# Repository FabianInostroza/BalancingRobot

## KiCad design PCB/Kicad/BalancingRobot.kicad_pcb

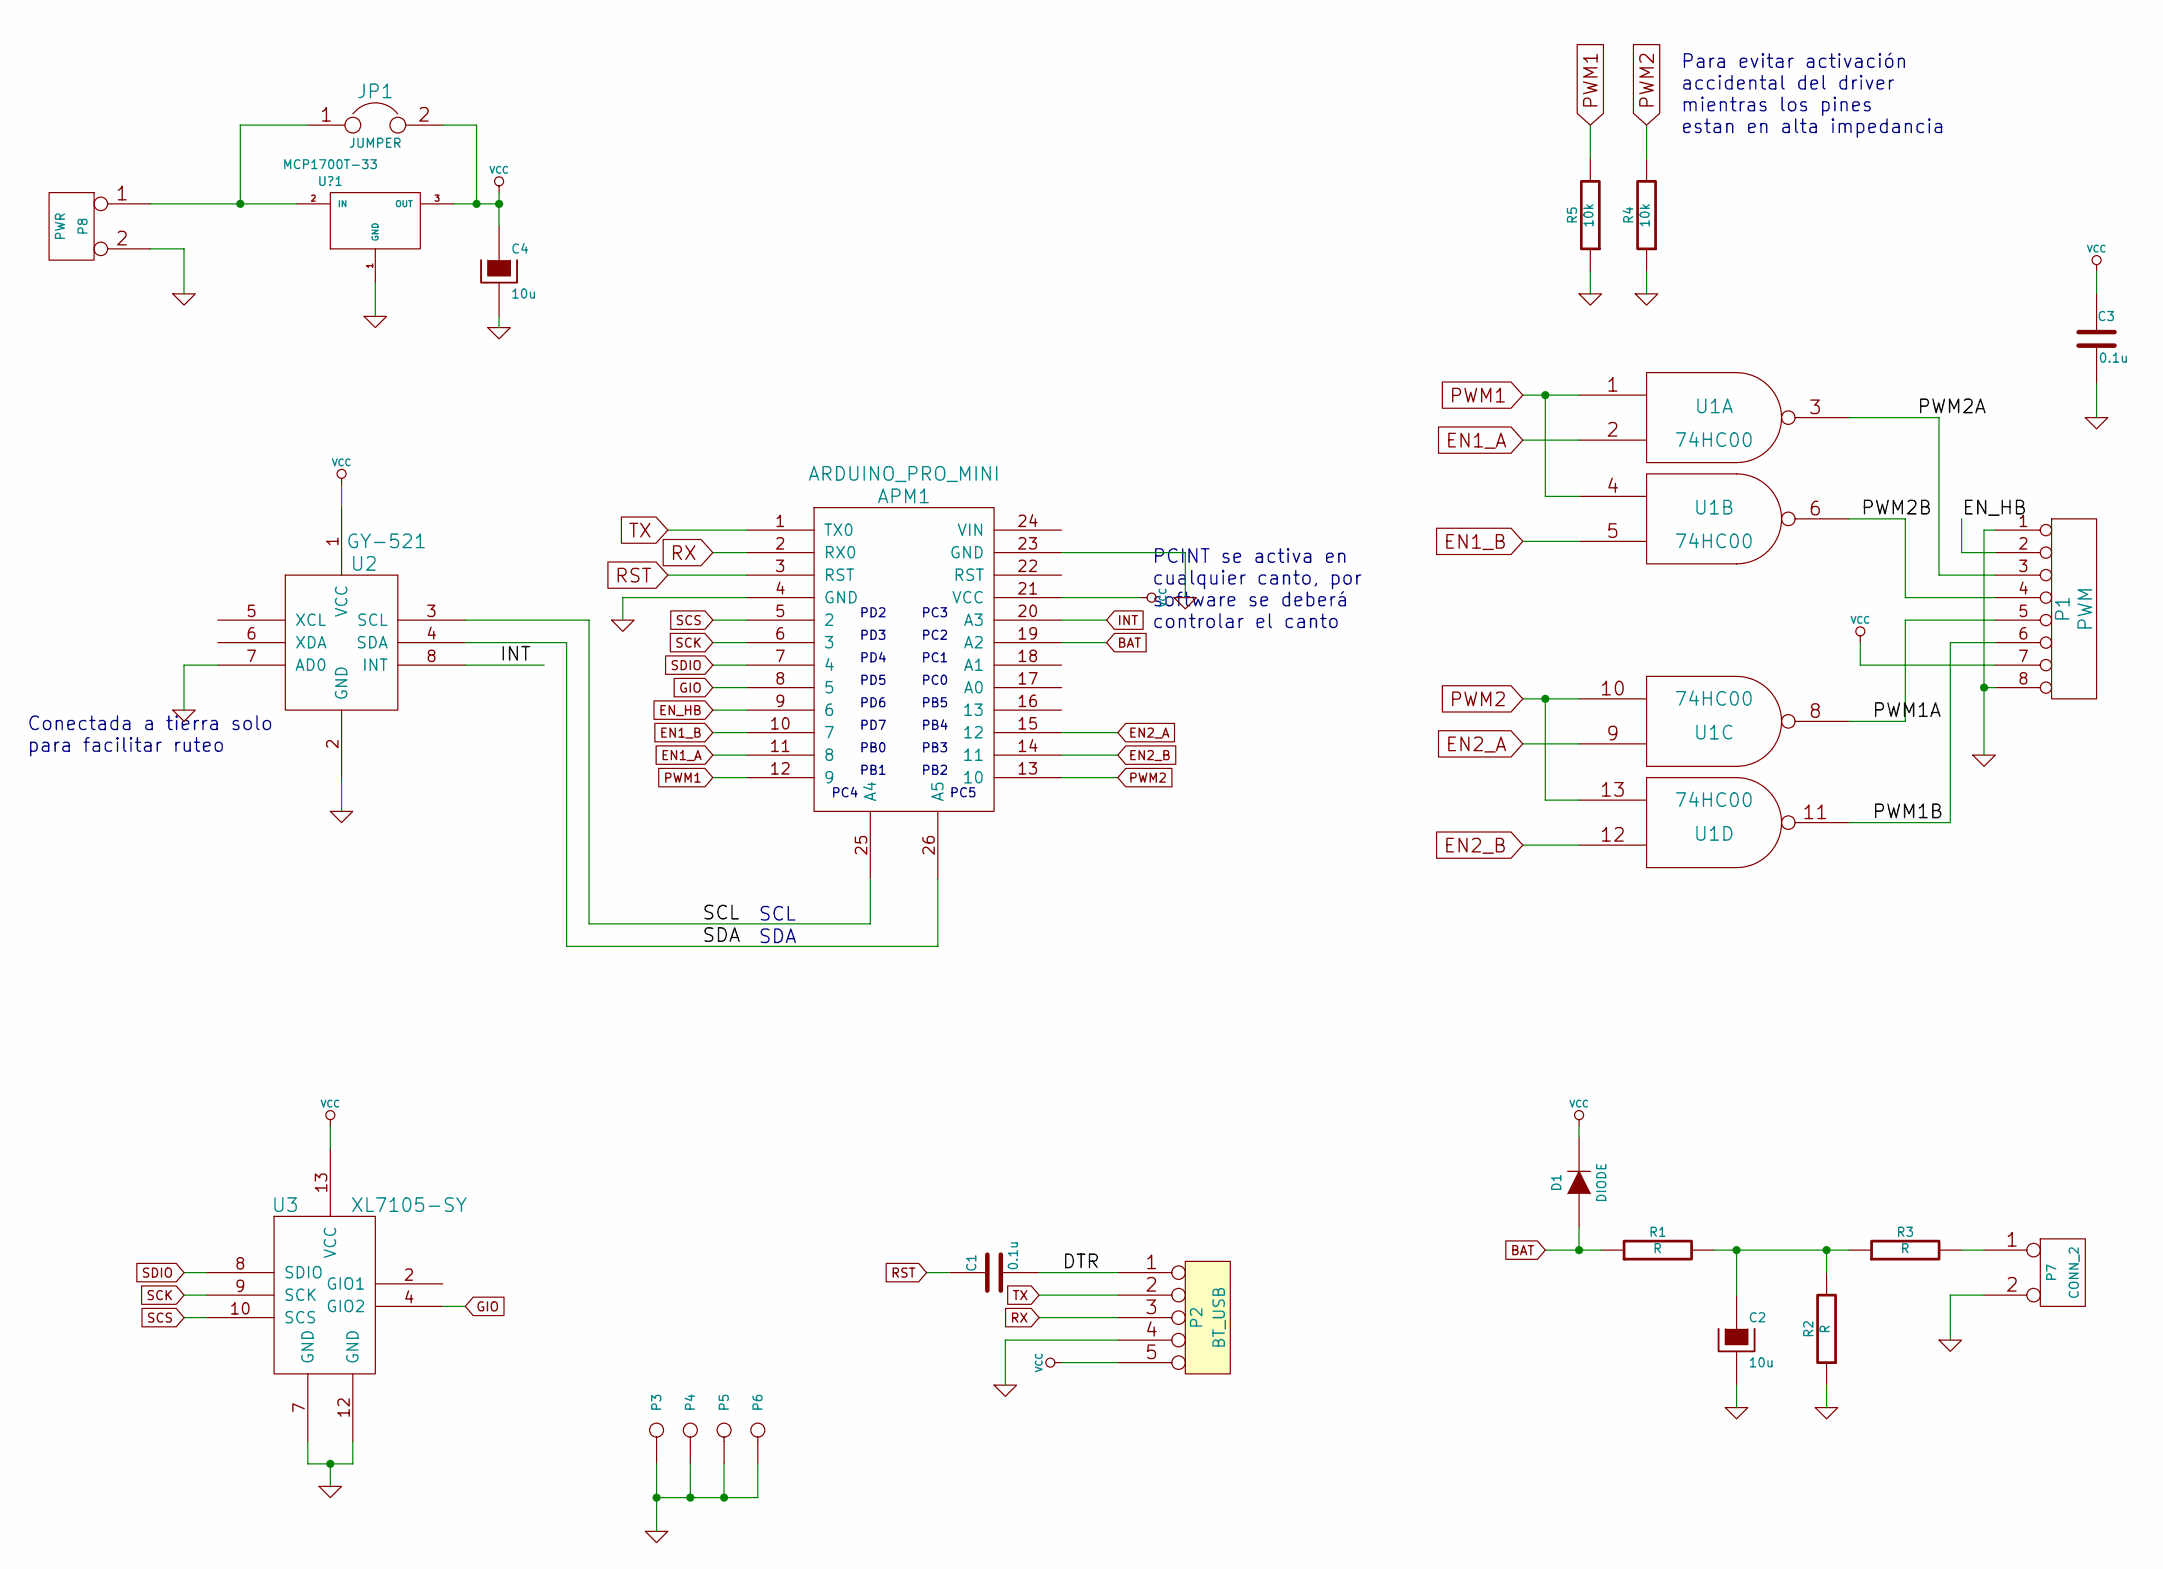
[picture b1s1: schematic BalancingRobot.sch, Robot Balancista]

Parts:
APM1: ARDUINO_PRO_MINI
C1, C3: 0.1u
C2, C4: 10u
D1: DIODE
JP1: JUMPER
P1: PWM
P2: BT_USB
P3, P4, P5, P6: CONN_1
P7: CONN_2
P8: PWR
R1, R2, R3: R
R4, R5: 10k
U1: 74HC00
U2: GY-521
U3: XL7105-SY
U?1: MCP1700T-33

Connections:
/DTR: C1.2, P2.1
/PWM1A: P1.5, U1.8
/PWM1B: P1.6, U1.11
/PWM2A: P1.3, U1.3
/PWM2B: P1.4, U1.6
/SCL: APM1.25 (A4), U2.3 (SCL)
/SDA: APM1.26 (A5), U2.4 (SDA)
BAT: APM1.19 (A2), D1.1 (A), R1.1
EN1_A: APM1.11 (8), U1.2
EN1_B: APM1.10 (7), U1.5
EN2_A: APM1.15 (12), U1.9
EN2_B: APM1.14 (11), U1.12
EN_HB: APM1.9 (6), P1.2
GIO: APM1.8 (5), U3.4 (GIO2)
GND: APM1.4 (GND), APM1.23 (GND), C2.2, C3.2, C4.2, P1.1, P1.8, P2.4, P3.1, P4.1, P5.1, P6.1, P7.2 (PM), P8.2 (PM), R2.1, R4.1, R5.1, U1.7 (GND), U2.2 (GND), U2.7 (AD0), U3.7 (GND), U3.12 (GND), U?1.1 (GND)
INT: APM1.20 (A3), U2.8 (INT)
unnamed: P7.1, R3.2
unnamed: C2.1, R1.2, R2.2, R3.1
unnamed: JP1.1, P8.1, U?1.2 (IN)
PWM1: APM1.12 (9), R5.2, U1.1, U1.4
PWM2: APM1.13 (10), R4.2, U1.10, U1.13
RST: APM1.3 (RST), C1.1
RX: APM1.2 (RX0), P2.3
SCK: APM1.6 (3), U3.9 (SCK)
SCS: APM1.5 (2), U3.10 (SCS)
SDIO: APM1.7 (4), U3.8 (SDIO)
TX: APM1.1 (TX0), P2.2
VCC: APM1.21 (VCC), C3.1, C4.1, D1.2 (K), JP1.2, P1.7, P2.5, U1.14 (VCC), U2.1 (VCC), U3.13 (VCC), U?1.3 (OUT)

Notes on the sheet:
SDA
SCL
Conectada a tierra solo para facilitar ruteo
PCINT se activa en cualquier canto, por software se deberá controlar el canto
PD2
PD3
PD4
PD5
PD6
PD7
PB0
PB1
PC3
PC2
PC1
PC0
PB5
PB4
PB3
PB2
PC4
PC5
Para evitar activación accidental del driver mientras los pines estan en alta impedancia

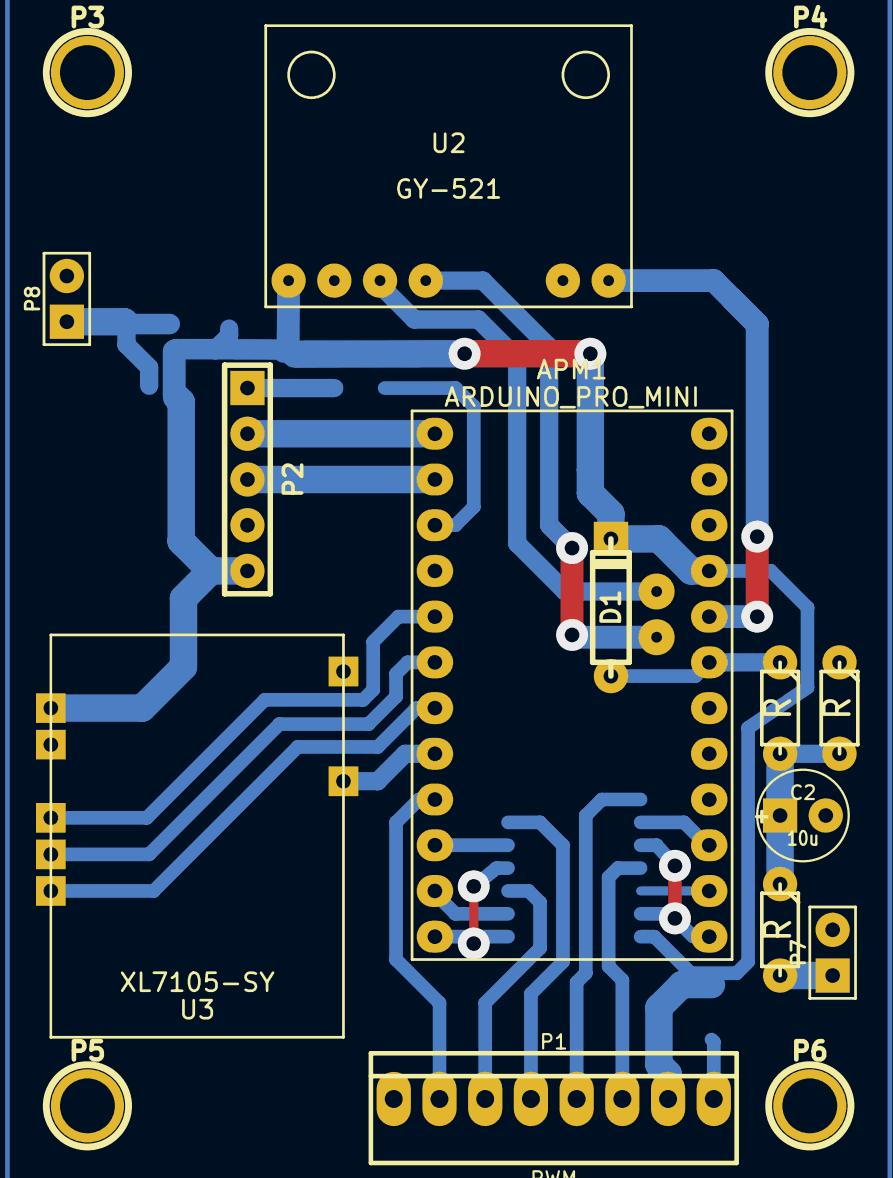
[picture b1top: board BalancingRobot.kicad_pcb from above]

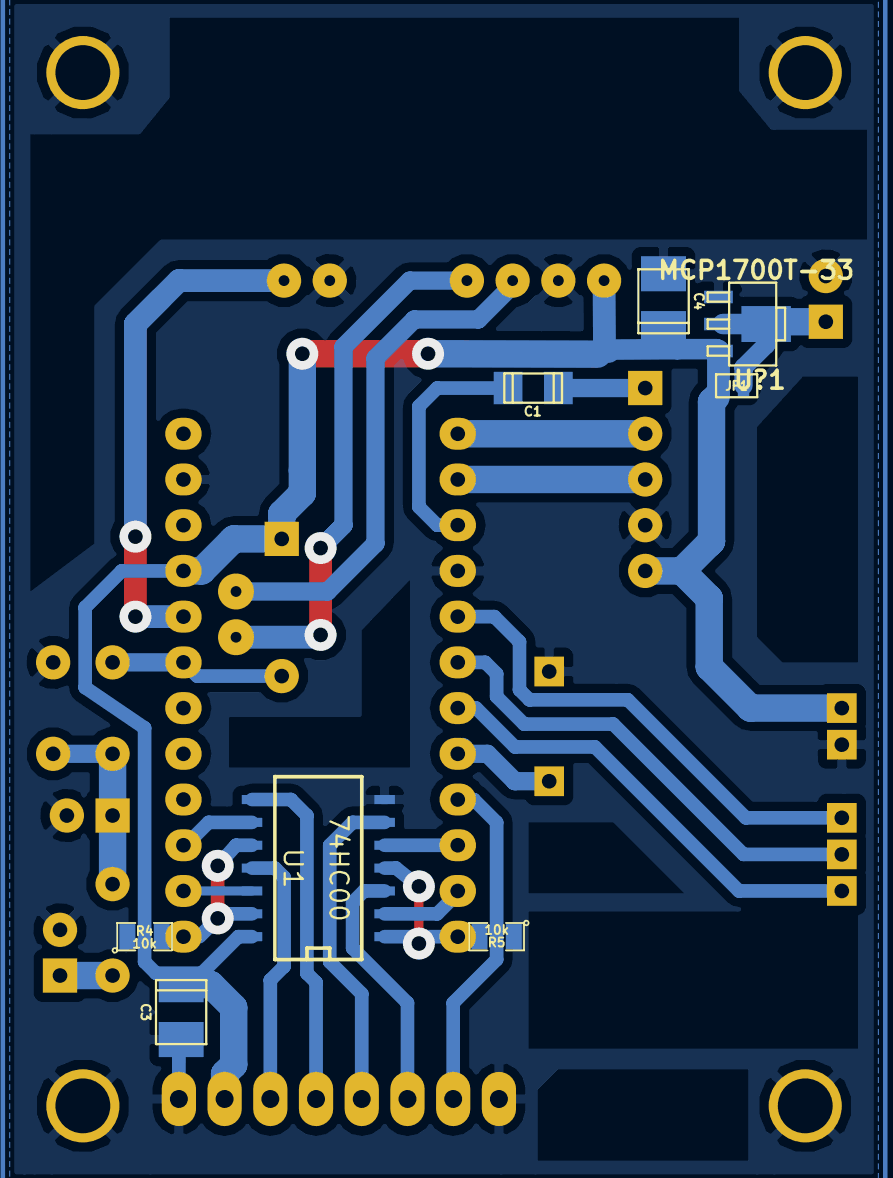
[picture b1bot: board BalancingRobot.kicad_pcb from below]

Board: 2 copper layers, 24 parts (8 on the bottom side), 28 nets.

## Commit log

2015-01-22 exclusion del ejecutable
2015-01-22 exclusion del qtserialport-build
2015-01-22 Cambio de carpeta
2015-01-22 adasd
2015-01-22 adas
2015-01-22 ADAS2
2015-01-22 add qtserialport
2015-01-23 Corregido problema en inicializacion de giroscopio(se activaba el self-test del eje X
2015-01-25 Implementacion de anulacion de offset en gyros
2015-01-26 Filtro complementario funcionando, draft de controlador de motor y de robot
2015-01-26 Agregada carpeta de info
2015-01-27 Driver de motor y primer controlador
2015-01-30 solucion Problema pl2303 (agregar retardo en inicializaccion uart), problema con fprintf y flotantes cuando codigo esta en la region superior de la memoria (ftoa_engine usa tabla que no puede leer), 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
2015-01-31 Agregado proyecto para robot mini
2015-01-31 Calculo y seteo del offset del acelerometro ok
2015-02-01 Cambios en la forma del controlador
2015-02-01 asdas
2015-02-02 interfaz serial pa cambiar parametros del controlador (no terminada)
2015-02-04 copia de robotmini a robot y agrupacion de librerias interfaz grafica en carpeta separada
2015-02-04 Interfaz para el robot
2015-02-05 cambios interfaz y codigo micro
2015-02-07 NUEVO PID, NO TERMINADO
2015-02-08 nuevo controlador, sin probar
2015-02-08 Controlador probado, parametros iniciales kc=-600, ti = 114, td = -500 (en la interfaz)
2015-02-11 modificaciones a la interfaz y codigo del micro para poder cambiar el sp (angulo) por interfaz serial
2015-02-14 Robot de balancea ok, ajustar mejor y calibrar bien el acelerometros
2015-02-15 Modificacion para que el pwm inicie apagado (todos los canales en 0), y para controlar direccion
2015-02-15 ignorar makefile de InterfazRobot (autogenerado)
2015-02-17 se agrego control por joystick inalambrico usando el XL7105, para que el micro envie datos (angulo, pwm, derror) hay que enviar un comando T y para que pare t, se agregaron parametros para el pid usa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
2015-02-17 Interfaz grafica muestra angulo de inclinacion multiplicado por 10
2015-02-23 Actualizacion de las constantes de calibracion del MPU6050, disminucion del ancho de banda del acelerometro y gyro (de aprox 180 a 98) mejoro el control, parametros para nuevo hardware
2015-02-23 Cambio en las variables para que variable pwm corresponda a la marca en los motores. Se agrego codigo que resetea el set point y el offset del pwm cuando se pierde la senal del mando
2015-02-23 Correccion en funcion twi_send y se agrego timeout a las demas funciones para que no bloqueen el programa en caso de error
2015-02-23 Se agrega funcion para resetear el buffer fifo y en la inicializacion ahora se verifica la direccion i2c del mpu6050
2015-02-23 Correccion del problema en el reinicio del microcontrolador que a veces hacia que los motores giraran aun cuando el angulo de inclinacion era mayor al limite. Se agrego codigo para indicar mediante e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
2015-02-24 Se agrega opcion para controlar el robot usando solamente el joystick izquierdo (presionar X+L2), solamente el joystick derecho (X+R2) o usando ambos joystick (izquierdo angulo, derecho direccion, X+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
2015-03-10 Diagrama de bloques
2015-04-16 se excluyen archivo aux de proteus
2015-04-16 se excluyen archivo aux de matlab
2015-04-16 Codigo para intentar usar atmega88 y modificacion de doc de filtros y modelo del robot
2015-04-16 Se agrego target para atmega328p (arduino mini)
2015-04-16 Cambio en el pin de interrupcion para hacer el codigo compatible con el atmega328p, falta arreglar el PWM
2015-08-08 pequeños cambios
2015-08-08 PCB para arduino mini, sin terminar
2015-08-09 primera version del PCB
2015-08-12 Diagramas
2015-08-14 Guardar datos de configuracion en flash y adaptacion para usar en atmega328p
2015-08-14 Se agrego otro target y se adaptó codigo para usar en atmega328p, falta terminar pwm y hacer que funcione todo
2015-08-14 Arreglo para que funcione en Arduino Pro Mini. Fix en calibracion del giroscopio para que no tarde tanto y active el watchdog
2015-08-14 carpetas de binarios
2015-08-14 arreglos y configuracion para que funcione en Arduino Pro Mini (328p)
2015-08-14 v1 del PCB y diagrama, primera version construida
2015-08-14 v1 del PCB y diagrama, primera version construida. se agregaron librerias faltantes
2015-08-15 Joystick (XL7105) ok. No se estaba leyendo correctamente la configuracion desde la flash
2015-08-17 Se agregaron resistencias pulldown en las señales PWM para que no se active el driver mientras el micro se esta iniciando
2015-08-17 Codigo ok, falta volver a sintonizar el controlador de angulo
2015-08-29 Version funcionando ok, controlador con ajuste aceptable, se cambio frecuencia de corte de filtro complementario
